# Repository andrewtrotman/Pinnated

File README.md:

# Pinnated
Experiments in building a 6809-based computer that can run FLEX from Compact Flash

# Unfinished
This project is experimental, unfinished, and known-broken in several ways.

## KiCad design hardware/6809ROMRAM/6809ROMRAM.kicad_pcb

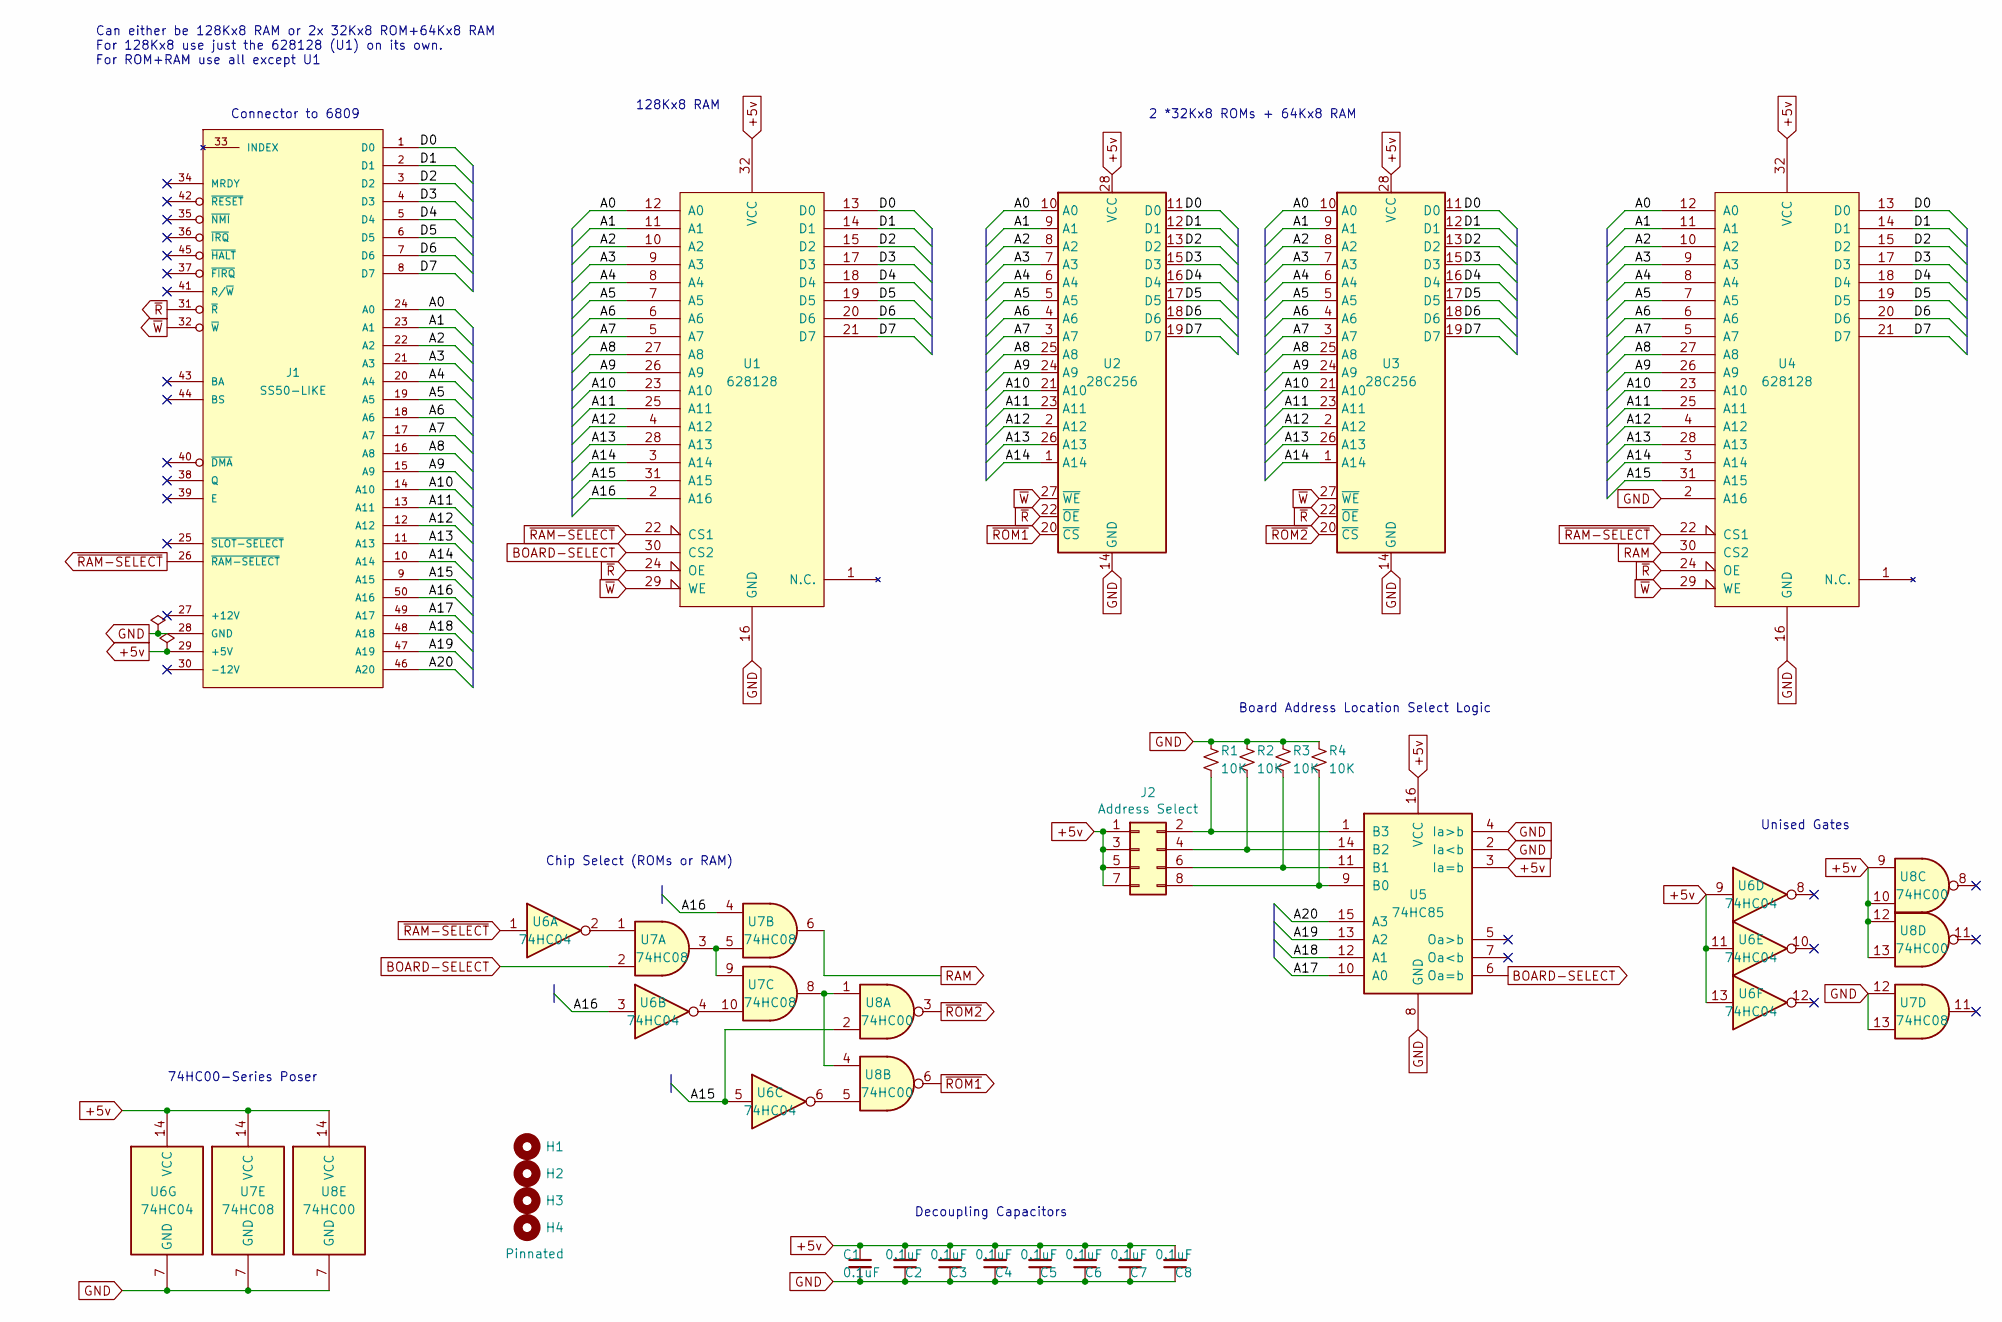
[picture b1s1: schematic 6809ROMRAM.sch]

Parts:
C1, C2, C3, C4, C5, C6, C7, C8: 0.1uF; C_Disc_D5.0mm_W2.5mm_P5.00mm
H1, H2, H3, H4: MountingHole; MountingHole_3.2mm_M3_ISO14580_Pad
J1: SS50-LIKE; PinHeader_2x25_P2.54mm_Vertical
J2: Address Select; PinHeader_2x04_P2.54mm_Vertical
Logo1: Pinnated; Pinnule
R1, R2, R3, R4: 10K; R_Axial_DIN0309_L9.0mm_D3.2mm_P12.70mm_Horizontal
U1, U4: 628128; DIP-32_W15.24mm_Socket_LongPads
U2, U3: 28C256; DIP-28_W15.24mm_Socket_LongPads
U5: 74HC85; DIP-16_W7.62mm_LongPads
U6: 74HC04; DIP-14_W7.62mm_LongPads
U7: 74HC08; DIP-14_W7.62mm_LongPads
U8: 74HC00; DIP-14_W7.62mm_LongPads

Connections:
+5v: C1.1, C2.2, C3.2, C4.2, C5.2, C6.2, C7.2, C8.2, J1.29 (+5V), J2.1, J2.3, J2.5, J2.7, U1.32 (VCC), U2.28 (VCC), U3.28 (VCC), U4.32 (VCC), U5.3 (Ia=b), U5.16 (VCC), U6.9, U6.11, U6.13, U6.14 (VCC), U7.14 (VCC), U8.9, U8.10, U8.12, U8.13, U8.14 (VCC)
/A0: J1.24 (A0), U1.12 (A0), U2.10 (A0), U3.10 (A0), U4.12 (A0)
/A1: J1.23 (A1), U1.11 (A1), U2.9 (A1), U3.9 (A1), U4.11 (A1)
/A2: J1.22 (A2), U1.10 (A2), U2.8 (A2), U3.8 (A2), U4.10 (A2)
/A3: J1.21 (A3), U1.9 (A3), U2.7 (A3), U3.7 (A3), U4.9 (A3)
/A4: J1.20 (A4), U1.8 (A4), U2.6 (A4), U3.6 (A4), U4.8 (A4)
/A5: J1.19 (A5), U1.7 (A5), U2.5 (A5), U3.5 (A5), U4.7 (A5)
/A6: J1.18 (A6), U1.6 (A6), U2.4 (A6), U3.4 (A6), U4.6 (A6)
/A7: J1.17 (A7), U1.5 (A7), U2.3 (A7), U3.3 (A7), U4.5 (A7)
/A8: J1.16 (A8), U1.27 (A8), U2.25 (A8), U3.25 (A8), U4.27 (A8)
/A9: J1.15 (A9), U1.26 (A9), U2.24 (A9), U3.24 (A9), U4.26 (A9)
/A10: J1.14 (A10), U1.23 (A10), U2.21 (A10), U3.21 (A10), U4.23 (A10)
/A11: J1.13 (A11), U1.25 (A11), U2.23 (A11), U3.23 (A11), U4.25 (A11)
/A12: J1.12 (A12), U1.4 (A12), U2.2 (A12), U3.2 (A12), U4.4 (A12)
/A13: J1.11 (A13), U1.28 (A13), U2.26 (A13), U3.26 (A13), U4.28 (A13)
/A14: J1.10 (A14), U1.3 (A14), U2.1 (A14), U3.1 (A14), U4.3 (A14)
/A15: J1.9 (A15), U1.31 (A15), U4.31 (A15), U6.5, U8.2
/A16: J1.50 (A16), U1.2 (A16), U6.3, U7.4
/A17: J1.49 (A17), U5.10 (A0)
/A18: J1.48 (A18), U5.12 (A1)
/A19: J1.47 (A19), U5.13 (A2)
/A20: J1.46 (A20), U5.15 (A3)
/D0: J1.1 (D0), U1.13 (D0), U2.11 (D0), U3.11 (D0), U4.13 (D0)
/D1: J1.2 (D1), U1.14 (D1), U2.12 (D1), U3.12 (D1), U4.14 (D1)
/D2: J1.3 (D2), U1.15 (D2), U2.13 (D2), U3.13 (D2), U4.15 (D2)
/D3: J1.4 (D3), U1.17 (D3), U2.15 (D3), U3.15 (D3), U4.17 (D3)
/D4: J1.5 (D4), U1.18 (D4), U2.16 (D4), U3.16 (D4), U4.18 (D4)
/D5: J1.6 (D5), U1.19 (D5), U2.17 (D5), U3.17 (D5), U4.19 (D5)
/D6: J1.7 (D6), U1.20 (D6), U2.18 (D6), U3.18 (D6), U4.20 (D6)
/D7: J1.8 (D7), U1.21 (D7), U2.19 (D7), U3.19 (D7), U4.21 (D7)
BOARD-SELECT: U1.30 (CS2), U5.6 (Oa=b), U7.2
GND: C1.2, C2.1, C3.1, C4.1, C5.1, C6.1, C7.1, C8.1, J1.28 (GND), R1.1, R2.1, R3.1, R4.1, U1.16 (GND), U2.14 (GND), U3.14 (GND), U4.2 (A16), U4.16 (GND), U5.2 (Ia<b), U5.4 (Ia>b), U5.8 (GND), U6.7 (GND), U7.7 (GND), U7.12, U7.13, U8.7 (GND)
unnamed: J2.2, R1.2, U5.1 (B3)
unnamed: J2.4, R2.2, U5.14 (B2)
unnamed: J2.6, R3.2, U5.11 (B1)
unnamed: J2.8, R4.2, U5.9 (B0)
unnamed: U6.2, U7.1
unnamed: U6.4, U7.10
unnamed: U6.6, U8.5
unnamed: U7.3, U7.5, U7.9
unnamed: U7.8, U8.1, U8.4
RAM: U4.30 (CS2), U7.6
~R: J1.31 (~R), U1.24 (OE), U2.22 (~OE), U3.22 (~OE), U4.24 (OE)
~RAM-SELECT: J1.26 (~RAM-SELECT), U1.22 (CS1), U4.22 (CS1), U6.1
~ROM1: U2.20 (~CS), U8.6
~ROM2: U3.20 (~CS), U8.3
~W: J1.32 (~W), U1.29 (WE), U2.27 (~WE), U3.27 (~WE), U4.29 (WE)

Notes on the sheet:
Unised Gates
Decoupling Capacitors
74HC00-Series Poser
2 *32Kx8 ROMs + 64Kx8 RAM
128Kx8 RAM
Board Address Location Select Logic
Connector to 6809
Chip Select (ROMs or RAM)
Can either be 128Kx8 RAM or 2x 32Kx8 ROM+64Kx8 RAM For 128Kx8 use just the 628128 (U1) on its own. For ROM+RAM use all except U1

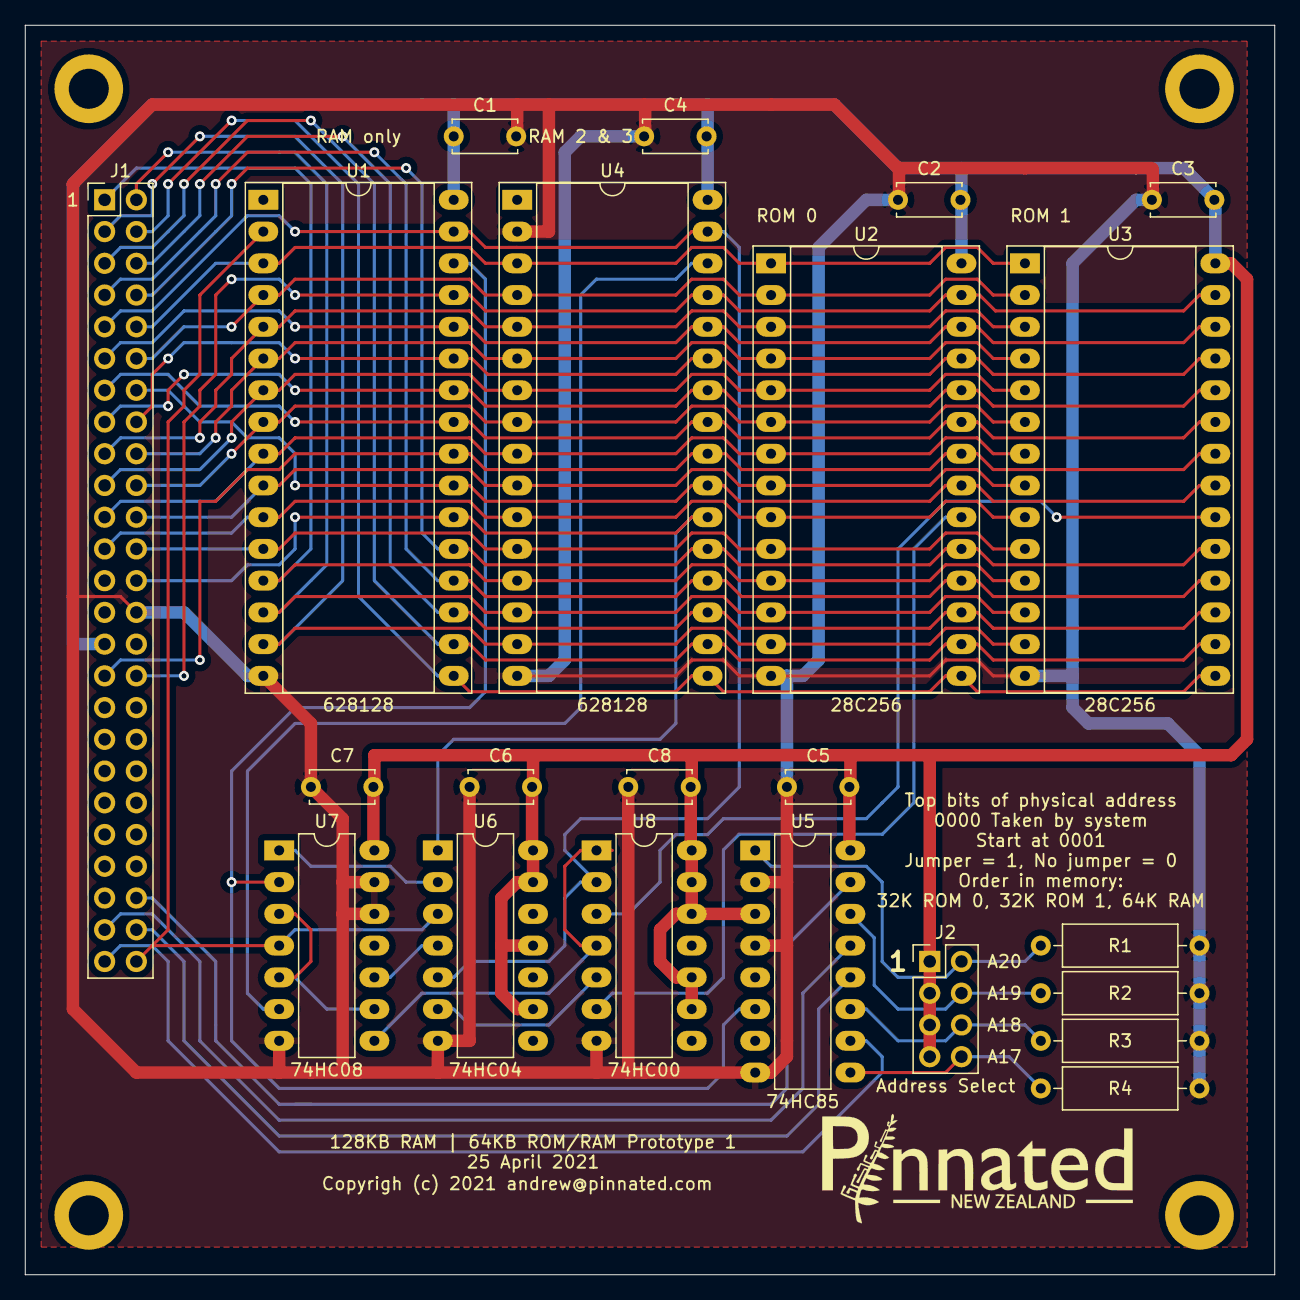
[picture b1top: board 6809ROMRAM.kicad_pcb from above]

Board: 2 copper layers, 100.0 x 100.0 mm, 27 parts (0 on the bottom side), 47 nets.

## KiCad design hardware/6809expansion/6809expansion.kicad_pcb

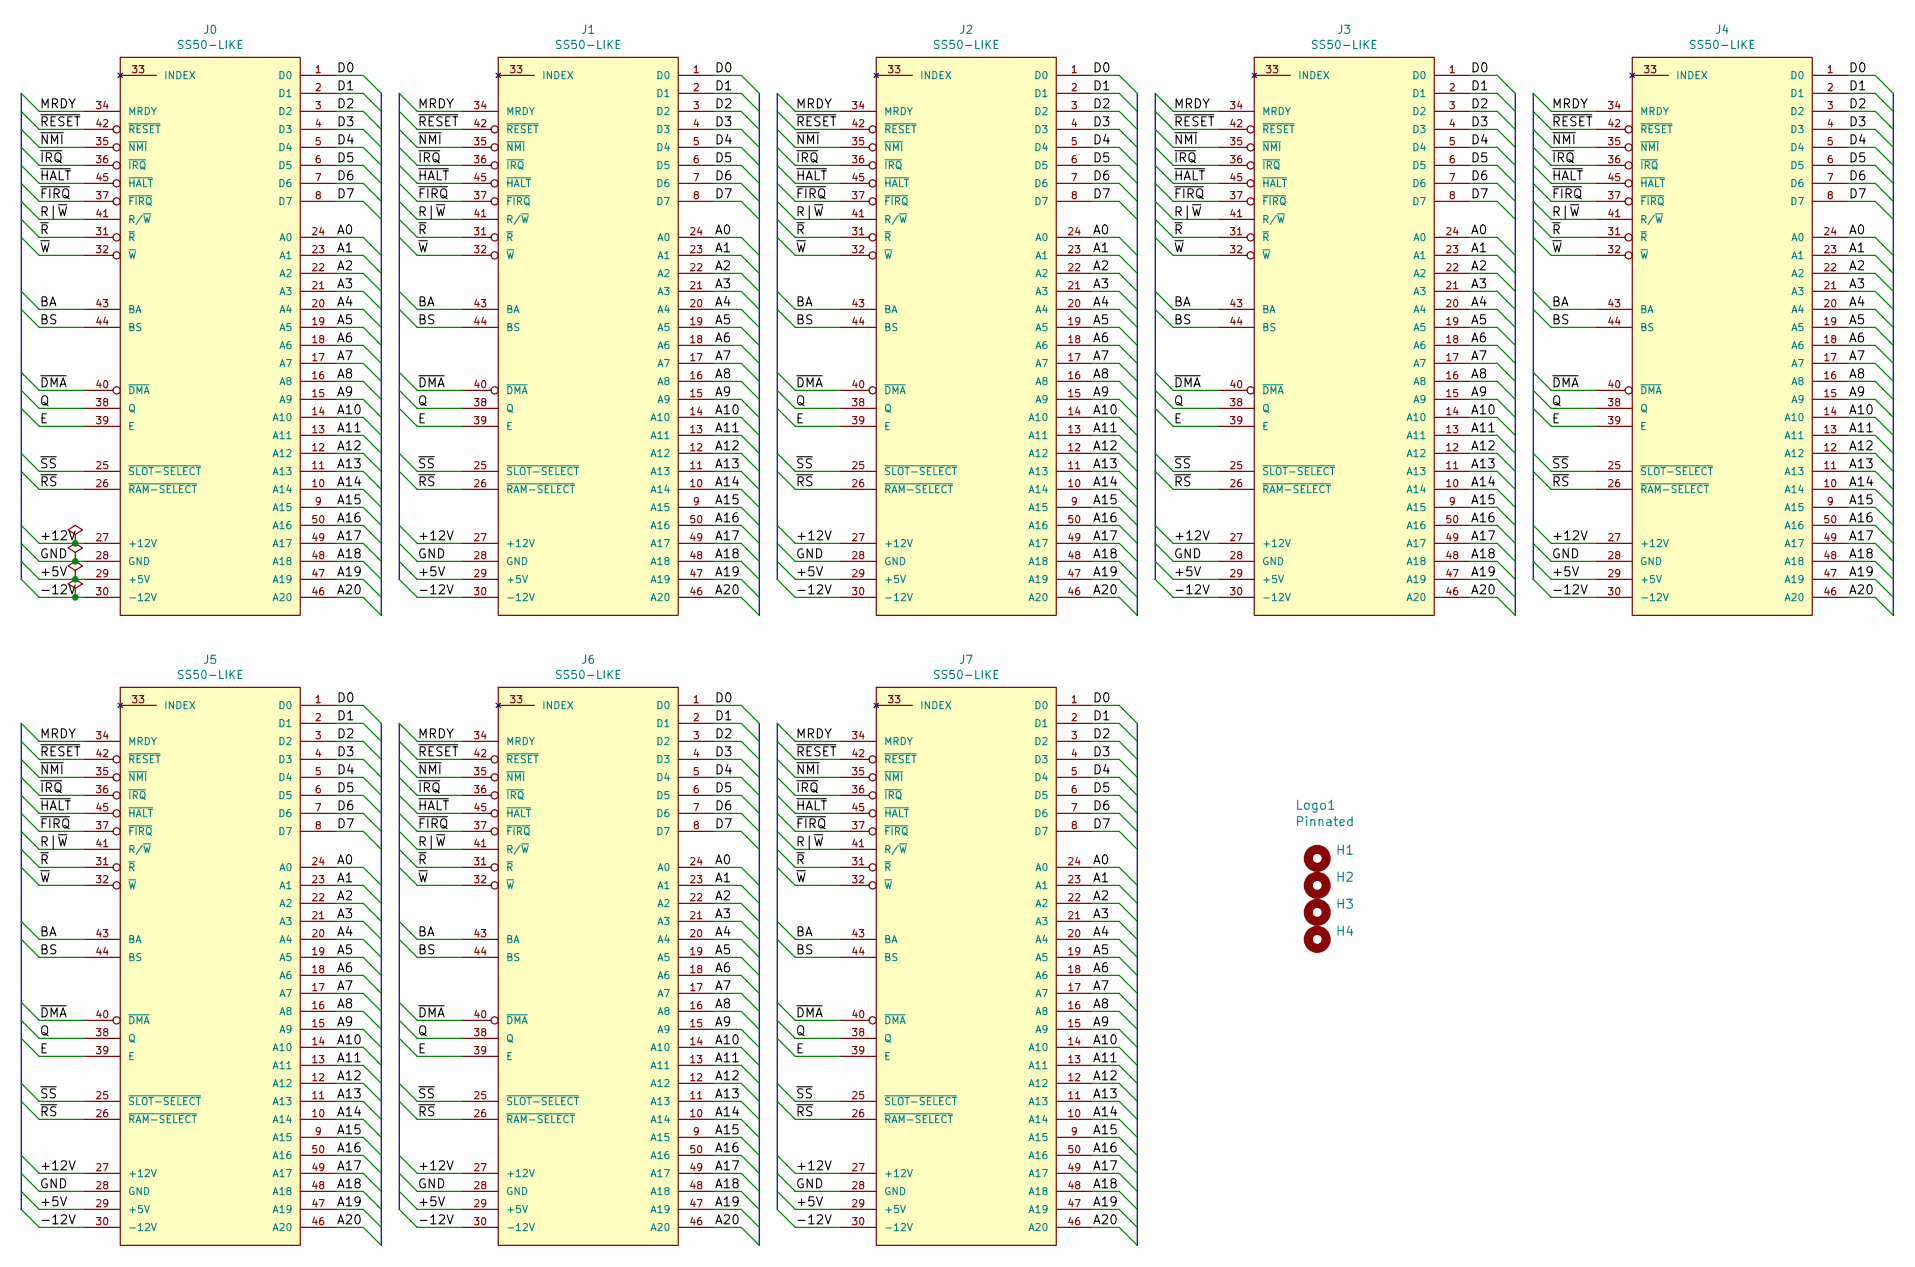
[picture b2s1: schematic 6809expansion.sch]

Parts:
H1, H2, H3, H4: MountingHole; MountingHole_3.2mm_M3_ISO14580_Pad
J0, J1, J2, J3, J4, J5, J6, J7: SS50-LIKE; IDC-Header_2x25_P2.54mm_Vertical
Logo1: Pinnated; Pinnule

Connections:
/+5V: J0.29 (+5V), J1.29 (+5V), J2.29 (+5V), J3.29 (+5V), J4.29 (+5V), J5.29 (+5V), J6.29 (+5V), J7.29 (+5V)
/+12V: J0.27 (+12V), J1.27 (+12V), J2.27 (+12V), J3.27 (+12V), J4.27 (+12V), J5.27 (+12V), J6.27 (+12V), J7.27 (+12V)
/-12V: J0.30 (-12V), J1.30 (-12V), J2.30 (-12V), J3.30 (-12V), J4.30 (-12V), J5.30 (-12V), J6.30 (-12V), J7.30 (-12V)
/A0: J0.24 (A0), J1.24 (A0), J2.24 (A0), J3.24 (A0), J4.24 (A0), J5.24 (A0), J6.24 (A0), J7.24 (A0)
/A1: J0.23 (A1), J1.23 (A1), J2.23 (A1), J3.23 (A1), J4.23 (A1), J5.23 (A1), J6.23 (A1), J7.23 (A1)
/A2: J0.22 (A2), J1.22 (A2), J2.22 (A2), J3.22 (A2), J4.22 (A2), J5.22 (A2), J6.22 (A2), J7.22 (A2)
/A3: J0.21 (A3), J1.21 (A3), J2.21 (A3), J3.21 (A3), J4.21 (A3), J5.21 (A3), J6.21 (A3), J7.21 (A3)
/A4: J0.20 (A4), J1.20 (A4), J2.20 (A4), J3.20 (A4), J4.20 (A4), J5.20 (A4), J6.20 (A4), J7.20 (A4)
/A5: J0.19 (A5), J1.19 (A5), J2.19 (A5), J3.19 (A5), J4.19 (A5), J5.19 (A5), J6.19 (A5), J7.19 (A5)
/A6: J0.18 (A6), J1.18 (A6), J2.18 (A6), J3.18 (A6), J4.18 (A6), J5.18 (A6), J6.18 (A6), J7.18 (A6)
/A7: J0.17 (A7), J1.17 (A7), J2.17 (A7), J3.17 (A7), J4.17 (A7), J5.17 (A7), J6.17 (A7), J7.17 (A7)
/A8: J0.16 (A8), J1.16 (A8), J2.16 (A8), J3.16 (A8), J4.16 (A8), J5.16 (A8), J6.16 (A8), J7.16 (A8)
/A9: J0.15 (A9), J1.15 (A9), J2.15 (A9), J3.15 (A9), J4.15 (A9), J5.15 (A9), J6.15 (A9), J7.15 (A9)
/A10: J0.14 (A10), J1.14 (A10), J2.14 (A10), J3.14 (A10), J4.14 (A10), J5.14 (A10), J6.14 (A10), J7.14 (A10)
/A11: J0.13 (A11), J1.13 (A11), J2.13 (A11), J3.13 (A11), J4.13 (A11), J5.13 (A11), J6.13 (A11), J7.13 (A11)
/A12: J0.12 (A12), J1.12 (A12), J2.12 (A12), J3.12 (A12), J4.12 (A12), J5.12 (A12), J6.12 (A12), J7.12 (A12)
/A13: J0.11 (A13), J1.11 (A13), J2.11 (A13), J3.11 (A13), J4.11 (A13), J5.11 (A13), J6.11 (A13), J7.11 (A13)
/A14: J0.10 (A14), J1.10 (A14), J2.10 (A14), J3.10 (A14), J4.10 (A14), J5.10 (A14), J6.10 (A14), J7.10 (A14)
/A15: J0.9 (A15), J1.9 (A15), J2.9 (A15), J3.9 (A15), J4.9 (A15), J5.9 (A15), J6.9 (A15), J7.9 (A15)
/A16: J0.50 (A16), J1.50 (A16), J2.50 (A16), J3.50 (A16), J4.50 (A16), J5.50 (A16), J6.50 (A16), J7.50 (A16)
/A17: J0.49 (A17), J1.49 (A17), J2.49 (A17), J3.49 (A17), J4.49 (A17), J5.49 (A17), J6.49 (A17), J7.49 (A17)
/A18: J0.48 (A18), J1.48 (A18), J2.48 (A18), J3.48 (A18), J4.48 (A18), J5.48 (A18), J6.48 (A18), J7.48 (A18)
/A19: J0.47 (A19), J1.47 (A19), J2.47 (A19), J3.47 (A19), J4.47 (A19), J5.47 (A19), J6.47 (A19), J7.47 (A19)
/A20: J0.46 (A20), J1.46 (A20), J2.46 (A20), J3.46 (A20), J4.46 (A20), J5.46 (A20), J6.46 (A20), J7.46 (A20)
/BA: J0.43 (BA), J1.43 (BA), J2.43 (BA), J3.43 (BA), J4.43 (BA), J5.43 (BA), J6.43 (BA), J7.43 (BA)
/BS: J0.44 (BS), J1.44 (BS), J2.44 (BS), J3.44 (BS), J4.44 (BS), J5.44 (BS), J6.44 (BS), J7.44 (BS)
/D0: J0.1 (D0), J1.1 (D0), J2.1 (D0), J3.1 (D0), J4.1 (D0), J5.1 (D0), J6.1 (D0), J7.1 (D0)
/D1: J0.2 (D1), J1.2 (D1), J2.2 (D1), J3.2 (D1), J4.2 (D1), J5.2 (D1), J6.2 (D1), J7.2 (D1)
/D2: J0.3 (D2), J1.3 (D2), J2.3 (D2), J3.3 (D2), J4.3 (D2), J5.3 (D2), J6.3 (D2), J7.3 (D2)
/D3: J0.4 (D3), J1.4 (D3), J2.4 (D3), J3.4 (D3), J4.4 (D3), J5.4 (D3), J6.4 (D3), J7.4 (D3)
/D4: J0.5 (D4), J1.5 (D4), J2.5 (D4), J3.5 (D4), J4.5 (D4), J5.5 (D4), J6.5 (D4), J7.5 (D4)
/D5: J0.6 (D5), J1.6 (D5), J2.6 (D5), J3.6 (D5), J4.6 (D5), J5.6 (D5), J6.6 (D5), J7.6 (D5)
/D6: J0.7 (D6), J1.7 (D6), J2.7 (D6), J3.7 (D6), J4.7 (D6), J5.7 (D6), J6.7 (D6), J7.7 (D6)
/D7: J0.8 (D7), J1.8 (D7), J2.8 (D7), J3.8 (D7), J4.8 (D7), J5.8 (D7), J6.8 (D7), J7.8 (D7)
/E: J0.39 (E), J1.39 (E), J2.39 (E), J3.39 (E), J4.39 (E), J5.39 (E), J6.39 (E), J7.39 (E)
/GND: J0.28 (GND), J1.28 (GND), J2.28 (GND), J3.28 (GND), J4.28 (GND), J5.28 (GND), J6.28 (GND), J7.28 (GND)
/MRDY: J0.34 (MRDY), J1.34 (MRDY), J2.34 (MRDY), J3.34 (MRDY), J4.34 (MRDY), J5.34 (MRDY), J6.34 (MRDY), J7.34 (MRDY)
/Q: J0.38 (Q), J1.38 (Q), J2.38 (Q), J3.38 (Q), J4.38 (Q), J5.38 (Q), J6.38 (Q), J7.38 (Q)
/R|~W: J0.41 (R/~W), J1.41 (R/~W), J2.41 (R/~W), J3.41 (R/~W), J4.41 (R/~W), J5.41 (R/~W), J6.41 (R/~W), J7.41 (R/~W)
/~DMA: J0.40 (~DMA), J1.40 (~DMA), J2.40 (~DMA), J3.40 (~DMA), J4.40 (~DMA), J5.40 (~DMA), J6.40 (~DMA), J7.40 (~DMA)
/~FIRQ: J0.37 (~FIRQ), J1.37 (~FIRQ), J2.37 (~FIRQ), J3.37 (~FIRQ), J4.37 (~FIRQ), J5.37 (~FIRQ), J6.37 (~FIRQ), J7.37 (~FIRQ)
/~HALT: J0.45 (~HALT), J1.45 (~HALT), J2.45 (~HALT), J3.45 (~HALT), J4.45 (~HALT), J5.45 (~HALT), J6.45 (~HALT), J7.45 (~HALT)
/~IRQ: J0.36 (~IRQ), J1.36 (~IRQ), J2.36 (~IRQ), J3.36 (~IRQ), J4.36 (~IRQ), J5.36 (~IRQ), J6.36 (~IRQ), J7.36 (~IRQ)
/~NMI: J0.35 (~NMI), J1.35 (~NMI), J2.35 (~NMI), J3.35 (~NMI), J4.35 (~NMI), J5.35 (~NMI), J6.35 (~NMI), J7.35 (~NMI)
/~R: J0.31 (~R), J1.31 (~R), J2.31 (~R), J3.31 (~R), J4.31 (~R), J5.31 (~R), J6.31 (~R), J7.31 (~R)
/~RESET: J0.42 (~RESET), J1.42 (~RESET), J2.42 (~RESET), J3.42 (~RESET), J4.42 (~RESET), J5.42 (~RESET), J6.42 (~RESET), J7.42 (~RESET)
/~RS: J0.26 (~RAM-SELECT), J1.26 (~RAM-SELECT), J2.26 (~RAM-SELECT), J3.26 (~RAM-SELECT), J4.26 (~RAM-SELECT), J5.26 (~RAM-SELECT), J6.26 (~RAM-SELECT), J7.26 (~RAM-SELECT)
/~SS: J0.25 (~SLOT-SELECT), J1.25 (~SLOT-SELECT), J2.25 (~SLOT-SELECT), J3.25 (~SLOT-SELECT), J4.25 (~SLOT-SELECT), J5.25 (~SLOT-SELECT), J6.25 (~SLOT-SELECT), J7.25 (~SLOT-SELECT)
/~W: J0.32 (~W), J1.32 (~W), J2.32 (~W), J3.32 (~W), J4.32 (~W), J5.32 (~W), J6.32 (~W), J7.32 (~W)

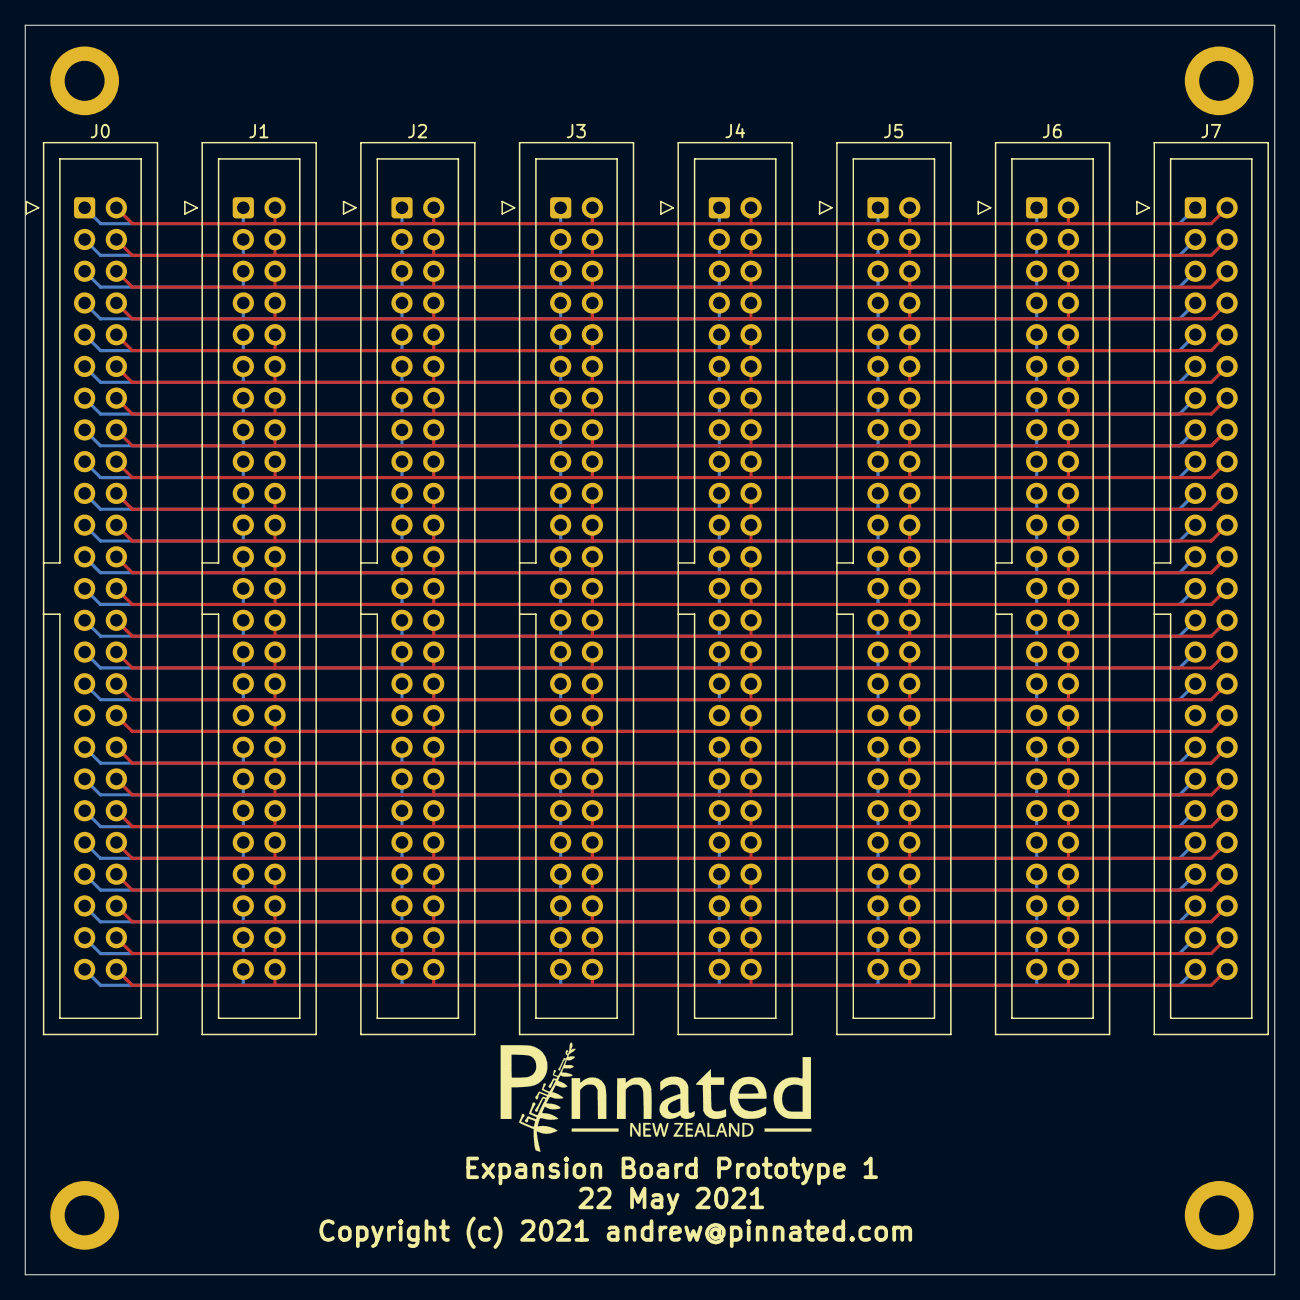
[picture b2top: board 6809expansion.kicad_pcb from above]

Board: 2 copper layers, 100.0 x 100.0 mm, 13 parts (0 on the bottom side), 49 nets.

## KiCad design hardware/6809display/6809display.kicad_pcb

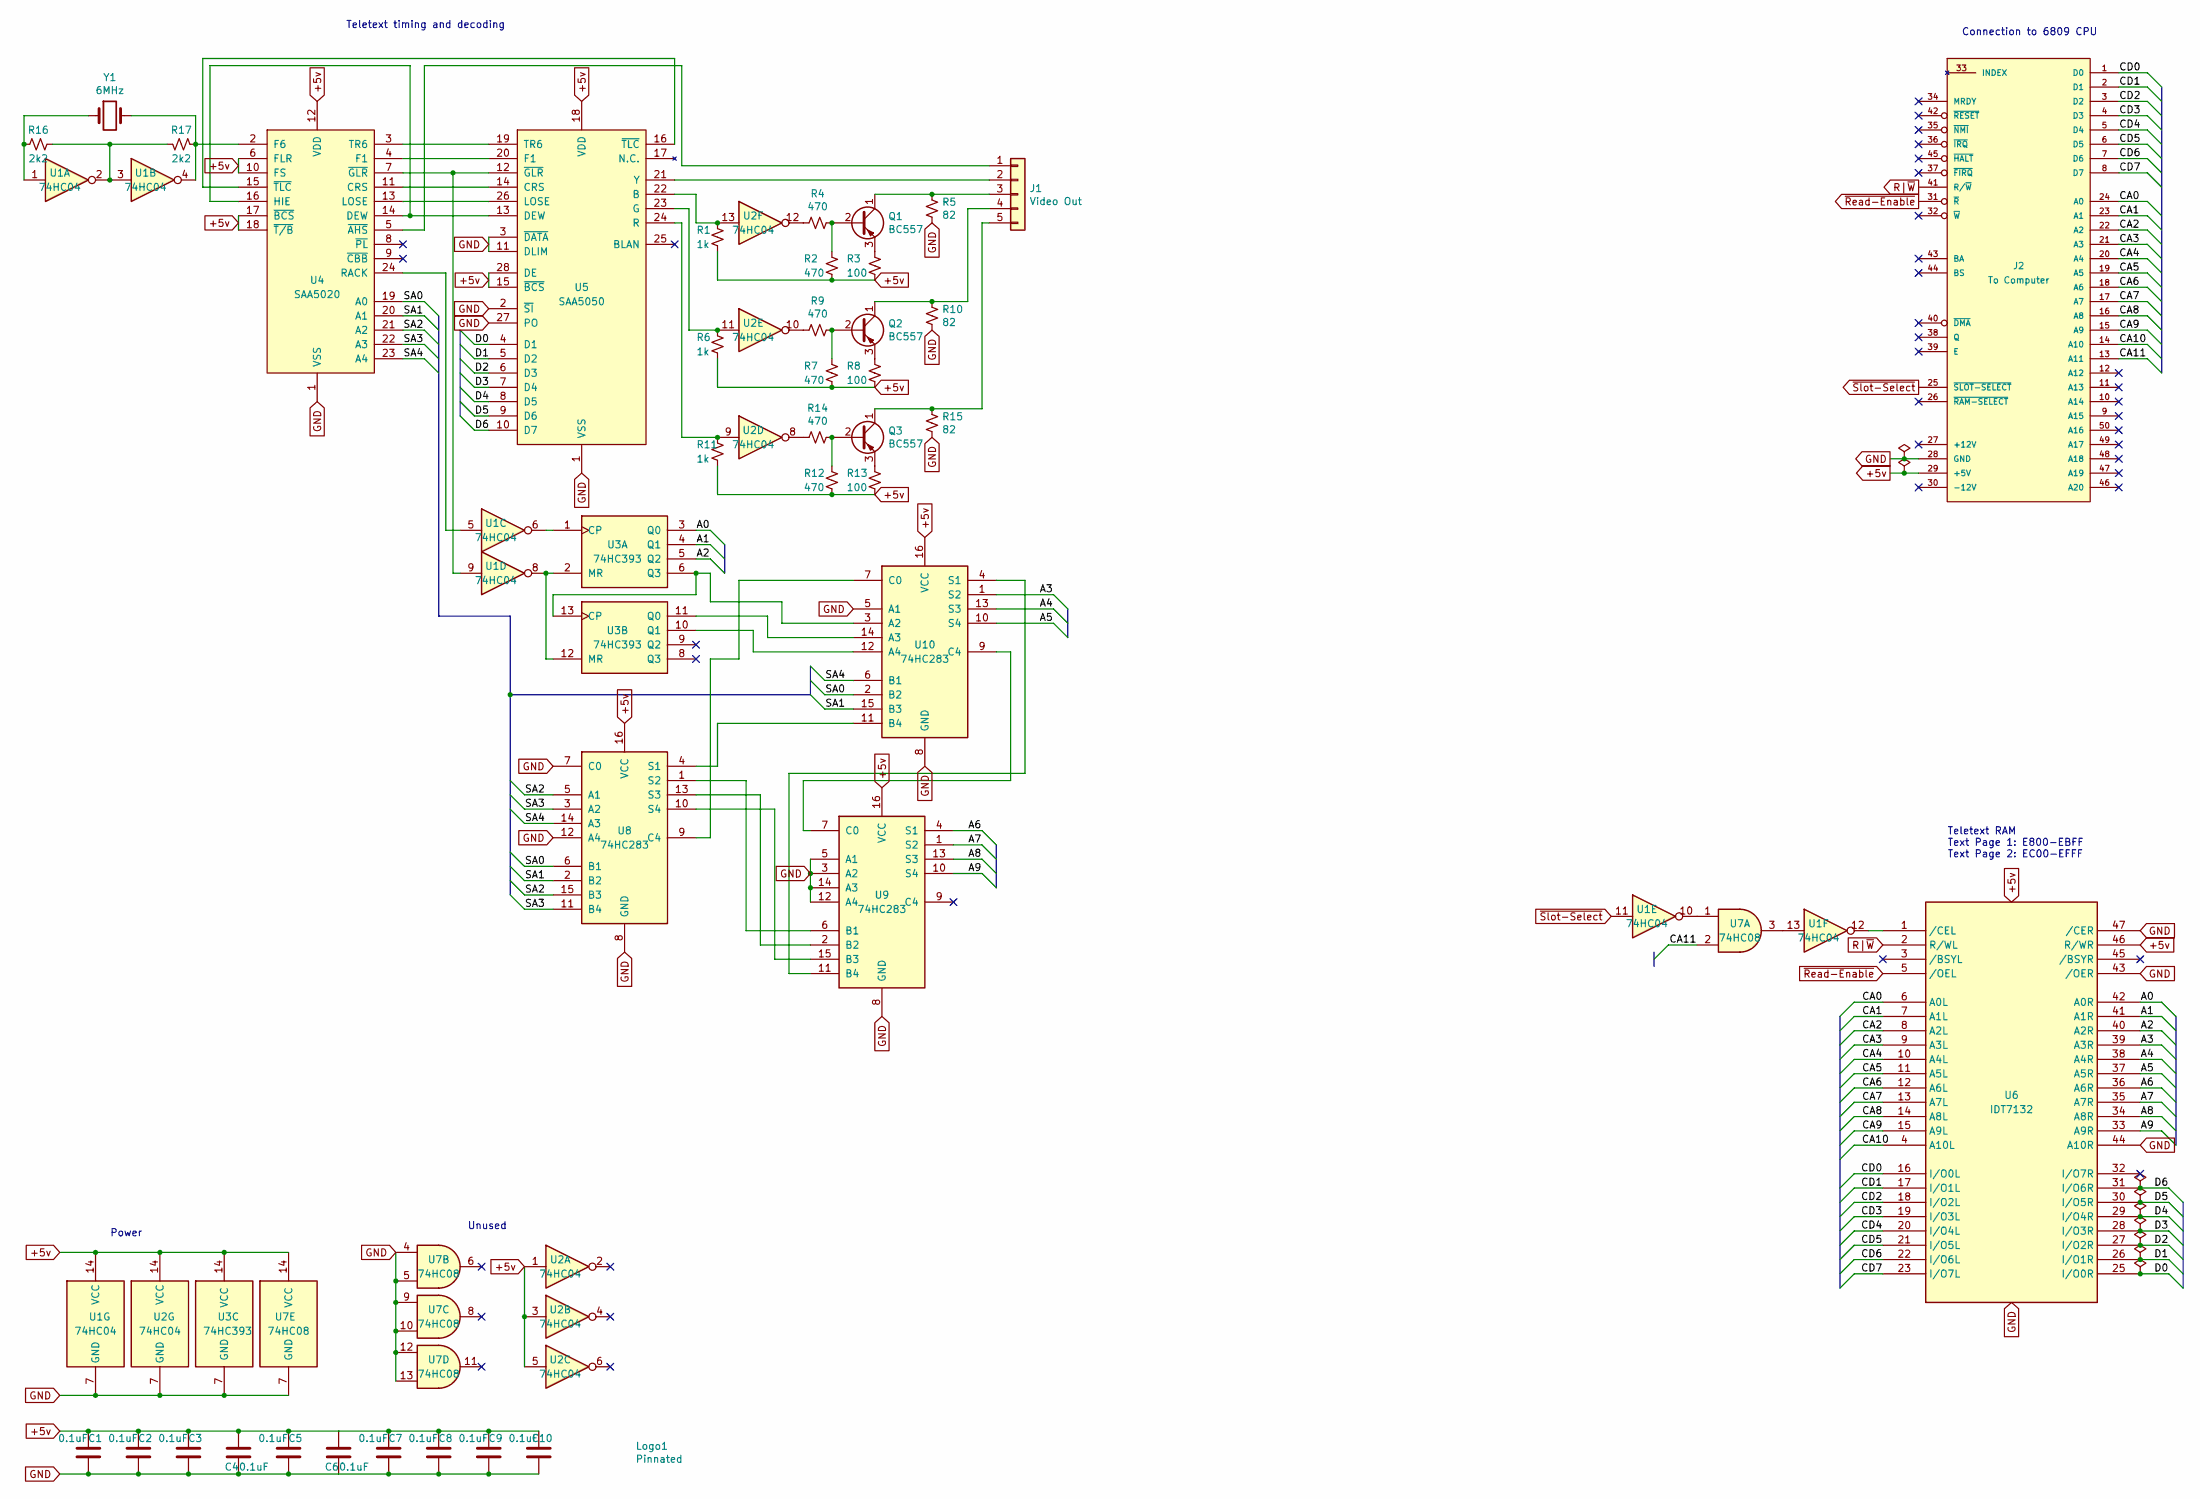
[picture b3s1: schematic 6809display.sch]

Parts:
C1, C2, C3, C4, C5, C6, C7, C8, C9, C10: 0.1uF; C_Disc_D5.0mm_W2.5mm_P5.00mm
J1: Video Out; PinHeader_1x05_P2.54mm_Vertical
J2: To Computer; IDC-Header_2x25_P2.54mm_Vertical
Logo1: Pinnated; Pinnule
Q1, Q2, Q3: BC557; TO-92_Inline_Wide
R1, R6, R11: 1k; R_Axial_DIN0207_L6.3mm_D2.5mm_P7.62mm_Horizontal
R2, R4, R7, R9, R12, R14: 470; R_Axial_DIN0207_L6.3mm_D2.5mm_P7.62mm_Horizontal
R3, R8, R13: 100; R_Axial_DIN0207_L6.3mm_D2.5mm_P7.62mm_Horizontal
R5, R10, R15: 82; R_Axial_DIN0207_L6.3mm_D2.5mm_P7.62mm_Horizontal
R16, R17: 2k2; R_Axial_DIN0207_L6.3mm_D2.5mm_P7.62mm_Horizontal
U1, U2: 74HC04; DIP-14_W7.62mm_Socket_LongPads
U3: 74HC393; DIP-14_W7.62mm_Socket_LongPads
U4: SAA5020; DIP-24_W15.24mm_Socket_LongPads
U5: SAA5050; DIP-28_W15.24mm_Socket_LongPads
U6: IDT7132; DIP-48_W15.24mm_Socket_LongPads
U7: 74HC08; DIP-14_W7.62mm_Socket_LongPads
U8, U9, U10: 74HC283; DIP-16_W7.62mm_Socket_LongPads
Y1: 6MHz; Resonator-2Pin_W7.0mm_H2.5mm

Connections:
+5v: C1.2, C2.2, C3.2, C4.1, C5.2, C6.1, C7.2, C8.2, C9.2, C10.2, J2.29 (+5V), R1.2, R2.2, R3.2, R6.2, R7.2, R8.2, R11.2, R12.2, R13.2, U1.14 (VCC), U2.1, U2.3, U2.5, U2.14 (VCC), U3.14 (VCC), U4.6 (FLR), U4.10 (FS), U4.12 (VDD), U4.17 (~BCS), U4.18 (~T/B), U5.15 (~BCS), U5.18 (VDD), U5.28 (DE), U6.46 (R/WR), U6.48 (VCC), U7.14 (VCC), U8.16 (VCC), U9.16 (VCC), U10.16 (VCC)
/A0: U3.3 (Q0), U6.42 (A0R)
/A1: U3.4 (Q1), U6.41 (A1R)
/A2: U3.5 (Q2), U6.40 (A2R)
/A3: U6.39 (A3R), U10.1 (S2)
/A4: U6.38 (A4R), U10.13 (S3)
/A5: U6.37 (A5R), U10.10 (S4)
/A6: U6.36 (A6R), U9.4 (S1)
/A7: U6.35 (A7R), U9.1 (S2)
/A8: U6.34 (A8R), U9.13 (S3)
/A9: U6.33 (A9R), U9.10 (S4)
/CA0: J2.24 (A0), U6.6 (A0L)
/CA1: J2.23 (A1), U6.7 (A1L)
/CA2: J2.22 (A2), U6.8 (A2L)
/CA3: J2.21 (A3), U6.9 (A3L)
/CA4: J2.20 (A4), U6.10 (A4L)
/CA5: J2.19 (A5), U6.11 (A5L)
/CA6: J2.18 (A6), U6.12 (A6L)
/CA7: J2.17 (A7), U6.13 (A7L)
/CA8: J2.16 (A8), U6.14 (A8L)
/CA9: J2.15 (A9), U6.15 (A9L)
/CA10: J2.14 (A10), U6.4 (A10L)
/CA11: J2.13 (A11), U7.2
/CD0: J2.1 (D0), U6.16 (I/O0L)
/CD1: J2.2 (D1), U6.17 (I/O1L)
/CD2: J2.3 (D2), U6.18 (I/O2L)
/CD3: J2.4 (D3), U6.19 (I/O3L)
/CD4: J2.5 (D4), U6.20 (I/O4L)
/CD5: J2.6 (D5), U6.21 (I/O5L)
/CD6: J2.7 (D6), U6.22 (I/O6L)
/CD7: J2.8 (D7), U6.23 (I/O7L)
/D0: U5.4 (D1), U6.25 (I/O0R)
/D1: U5.5 (D2), U6.26 (I/O1R)
/D2: U5.6 (D3), U6.27 (I/O2R)
/D3: U5.7 (D4), U6.28 (I/O3R)
/D4: U5.8 (D5), U6.29 (I/O4R)
/D5: U5.9 (D6), U6.30 (I/O5R)
/D6: U5.10 (D7), U6.31 (I/O6R)
/SA0: U4.19 (A0), U8.6 (B1), U10.2 (B2)
/SA1: U4.20 (A1), U8.2 (B2), U10.15 (B3)
/SA2: U4.21 (A2), U8.5 (A1), U8.15 (B3)
/SA3: U4.22 (A3), U8.3 (A2), U8.11 (B4)
/SA4: U4.23 (A4), U8.14 (A3), U10.6 (B1)
GND: C1.1, C2.1, C3.1, C4.2, C5.1, C6.2, C7.1, C8.1, C9.1, C10.1, J2.28 (GND), R5.2, R10.2, R15.2, U1.7 (GND), U2.7 (GND), U3.7 (GND), U4.1 (VSS), U5.1 (VSS), U5.2 (~SI), U5.3 (~DATA), U5.11 (DLIM), U5.27 (PO), U6.24 (GND), U6.43 (/OER), U6.44 (A10R), U6.47 (/CER), U7.4, U7.5, U7.7 (GND), U7.9, U7.10, U7.12, U7.13, U8.7 (C0), U8.8 (GND), U8.12 (A4), U9.3 (A2), U9.5 (A1), U9.8 (GND), U9.12 (A4), U9.14 (A3), U10.5 (A1), U10.8 (GND)
unnamed: J1.1, U4.5 (~AHS)
unnamed: J1.2, U5.21 (Y)
unnamed: J1.3, Q1.1 (C), R5.1
unnamed: J1.4, Q2.1 (C), R10.1
unnamed: J1.5, Q3.1 (C), R15.1
unnamed: Q1.2 (B), R2.1, R4.1
unnamed: Q1.3 (E), R3.1
unnamed: Q2.2 (B), R7.1, R9.1
unnamed: Q2.3 (E), R8.1
unnamed: Q3.2 (B), R12.1, R14.1
unnamed: Q3.3 (E), R13.1
unnamed: R1.1, U2.13, U5.22 (B)
unnamed: R4.2, U2.12
unnamed: R6.1, U2.11, U5.23 (G)
unnamed: R9.2, U2.10
unnamed: R11.1, U2.9, U5.24 (R)
unnamed: R14.2, U2.8
unnamed: R16.1, U1.1, Y1.1
unnamed: R16.2, R17.2, U1.2, U1.3
unnamed: R17.1, U1.4, U4.2 (F6), Y1.2
unnamed: U1.5, U4.24 (RACK)
unnamed: U1.6, U3.1 (CP)
unnamed: U1.8, U3.2 (MR), U3.12 (MR)
unnamed: U1.9, U4.7 (~GLR), U5.12 (~GLR)
unnamed: U1.10, U7.1
unnamed: U1.12, U6.1 (/CEL)
unnamed: U1.13, U7.3
unnamed: U4.3 (TR6), U5.19 (TR6)
unnamed: U4.4 (F1), U5.20 (F1)
unnamed: U4.11 (CRS), U5.14 (CRS)
unnamed: U4.13 (LOSE), U5.26 (LOSE)
unnamed: U4.14 (DEW), U4.16 (HIE), U5.13 (DEW)
unnamed: U4.15 (~TLC), U5.16 (~TLC)
unnamed: U8.1 (S2), U9.6 (B1)
unnamed: U8.10 (S4), U9.15 (B3)
unnamed: U8.13 (S3), U9.2 (B2)
unnamed: U3.6 (Q3), U3.13 (CP), U10.3 (A2)
unnamed: U9.11 (B4), U10.4 (S1)
unnamed: U8.9 (C4), U10.7 (C0)
unnamed: U9.7 (C0), U10.9 (C4)
unnamed: U8.4 (S1), U10.11 (B4)
unnamed: U3.10 (Q1), U10.12 (A4)
unnamed: U3.11 (Q0), U10.14 (A3)
R|~W: J2.41 (R/~W), U6.2 (R/WL)
~Read-Enable: J2.31 (~R), U6.5 (/OEL)
~Slot-Select: J2.25 (~SLOT-SELECT), U1.11

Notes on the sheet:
Teletext RAM Text Page 1: E800-EBFF Text Page 2: EC00-EFFF
Teletext timing and decoding
Connection to 6809 CPU
Unused
Power

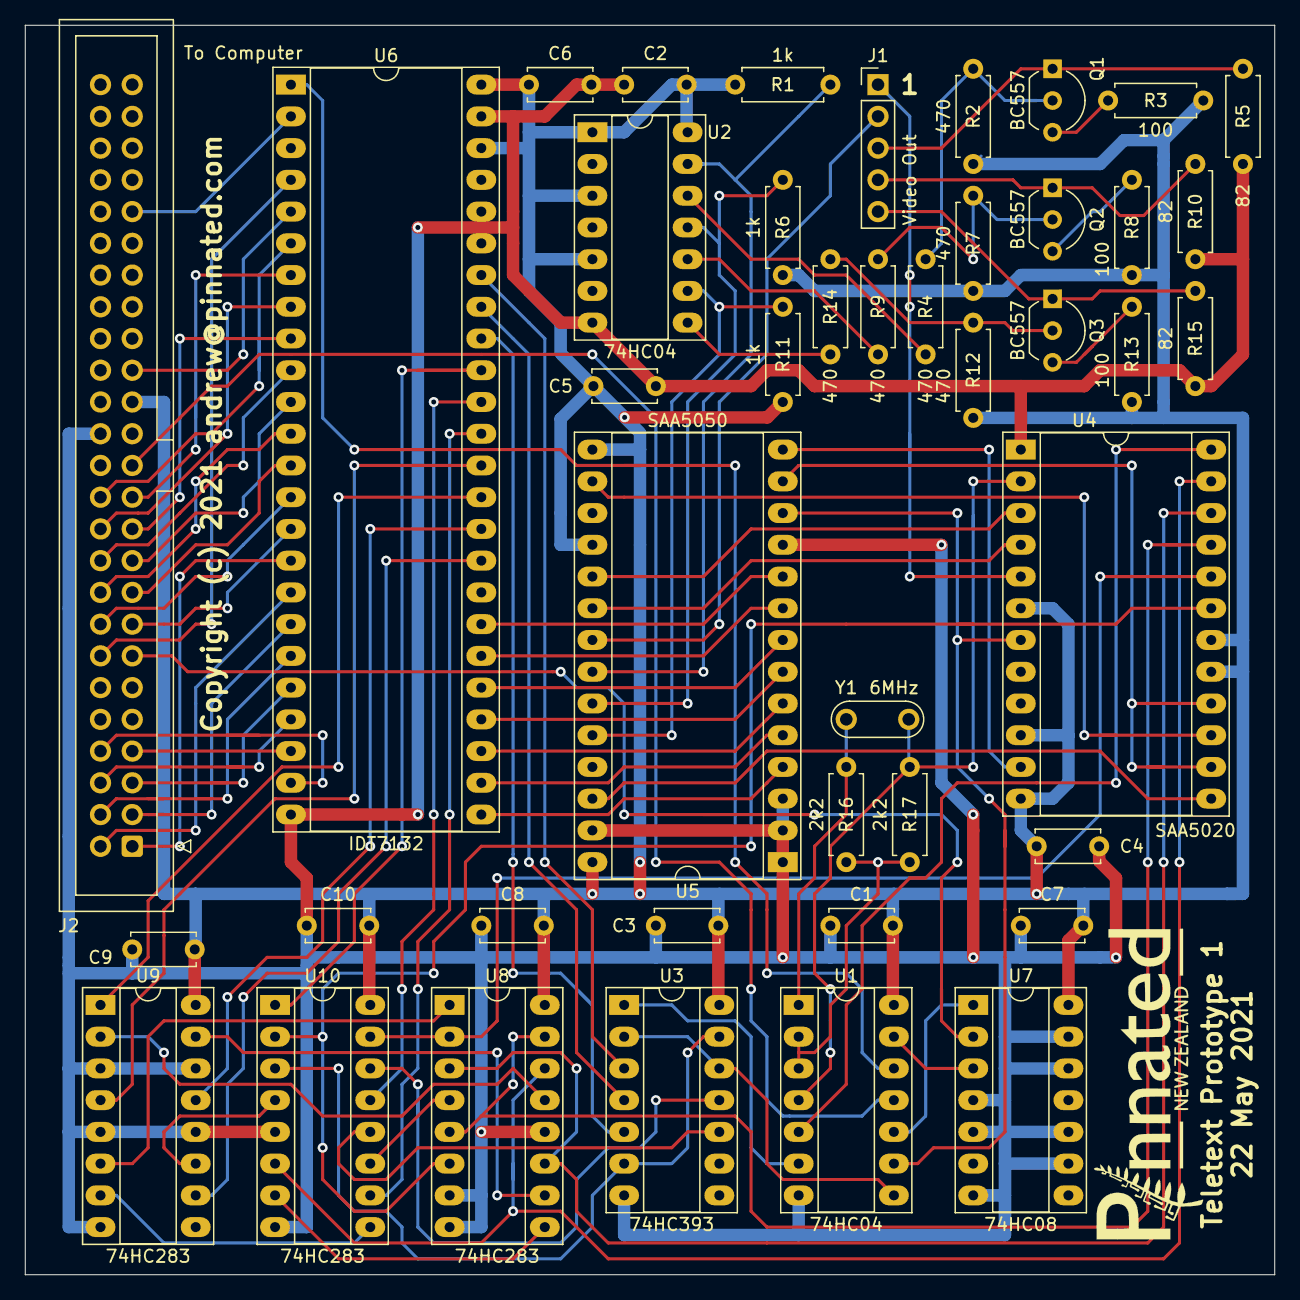
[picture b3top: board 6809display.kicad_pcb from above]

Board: 2 copper layers, 100.0 x 100.0 mm, 44 parts (0 on the bottom side), 90 nets.

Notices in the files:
hardware/6809/6809.kicad_pcb:
Copyright (c) 2021 andrew@pinnated.com
hardware/6809ROMRAM/6809ROMRAM.kicad_pcb:
Copyrigh (c) 2021 andrew@pinnated.com
